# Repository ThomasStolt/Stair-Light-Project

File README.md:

# Stair Light Project

Automatic animated stair lighting with **SK6812 RGBW** LEDs. Two PIR sensors (SR-HC501) at the first and last step detect direction and trigger a random animation. Control via a phone-friendly **web UI** (motion automation on/off, playing animations, fixed colour, device status, settings and birthdays) and optional **night mode** (configurable hours: soft red light only).

- **MCU:** ESP8266 (e.g. NodeMCU)
- **LEDs:** SK6812 RGBW (WS2812-compatible), 27 LEDs per step, 16 steps (configurable)
- **Sensors:** PIR1 = “up”, PIR2 = “down”
- **Boot:** Three soft green-white pulses (2 s) signal “ready”. Motion automation comes back as it was last set (on for a new device).

<div align="center">
  
</div>

---

## Requirements

- **Arduino CLI** (e.g. `brew install arduino-cli`)
- **ESP8266 core:**  
  `arduino-cli core update-index && arduino-cli core install esp8266:esp8266`
- **Libraries:**  
  `arduino-cli lib install "Adafruit NeoPixel"`  
  `arduino-cli lib install "EasyNTPClient"`

---

## Project structure

| Folder/File | Description |
|-------------|-------------|
| `rgbw_stair_light/` | Main sketch (stair light + OTA) |
| `rgbw_stair_light/parking.h` | Animations and helpers |
| `rgbw_stair_light/web_ui.h` | Web UI page (HTML/CSS/JS, served from flash) |
| `rgbw_stair_light/birthdays.h.example` | Template for birthdays (copy to `birthdays.h`) |
| `schematics/` | KiCad schematic, PCB |
| `images/` | Photos (incl. test bed) |

**Scripts (project root):**

| Script | Purpose |
|--------|---------|
| `upload-to-esp8266.sh` | Compile + upload **via USB** |
| `upload-to-esp8266-ota.sh` | Upload **via OTA** (WiFi) to one or more devices; compiles only when the sketch changed |
| `upload-ota-firewall-ok.sh` | OTA with **firewall temporarily disabled** (macOS) |
| `setup-firewall-ota.sh` | Add firewall rule for OTA (macOS, sudo) |

---

## Setup

### 1. WiFi and hostname

Credentials go in **`rgbw_stair_light/credentials.h`** (gitignored).

- Copy `credentials.h.example` to `credentials.h` and set:
  - `WIFI_SSID` – your Wi‑Fi name  
  - `WIFI_PASS` – Wi‑Fi password  
  - `OTA_HOSTNAME` – e.g. `stairlight-testbed` or `stairlight`

Without `credentials.h` the build fails.

> The hostname can also be changed at runtime in the web UI (**Settings** section); it is stored in flash and applied on the next reboot. `OTA_HOSTNAME` in `credentials.h` is only the default used on first boot.

### 2. Birthdays (optional)

On dates listed in **`rgbw_stair_light/birthdays.h`**, only the birthday animation runs.

- **`birthdays.h`** is in `.gitignore` and is not committed.
- Copy `birthdays.h.example` to `birthdays.h`, set `BIRTHDAY_COUNT` and the `BIRTHDAY(month, day)` list (e.g. `BIRTHDAY(3, 15)` = 15 March).
- Without `birthdays.h` the build fails – after cloning, copy the example (use 0 entries if you don’t need birthdays).

### 3. Firewall (macOS, only if OTA fails)

If OTA fails with the firewall on:

- **Option A – rule via CLI:**  
  `sudo ./setup-firewall-ota.sh`  
  (allows Arduino Python and Terminal/Cursor to accept incoming connections)

- **Option B – OTA with firewall briefly off:**  
  `./upload-ota-firewall-ok.sh stairlight-testbed.local`  
  (firewall is disabled only during the upload, then re-enabled)

---

## First upload: via USB

1. Connect the ESP8266 via USB.
2. Check port (optional):  
   `arduino-cli board list`
3. From the project folder run:

   ```bash
   ./upload-to-esp8266.sh
   ```

   Default port is `/dev/cu.usbserial-0001`. To use another port:

   ```bash
   ./upload-to-esp8266.sh /dev/cu.wchusbserial-12345
   ```

4. After a successful upload the ESP connects to Wi‑Fi and is ready for OTA.

---

## Upload via OTA (WiFi)

Prerequisite: the ESP is already running firmware with **ArduinoOTA** (e.g. after the first USB upload) and is on the same Wi‑Fi network. The OTA script uses **espota.py** (no board discovery required); pass the ESP’s IP or mDNS hostname.

- **By hostname (mDNS):**  
  ```bash
  ./upload-to-esp8266-ota.sh stairlight-testbed.local
  ```

- **By IP:**  
  ```bash
  ./upload-to-esp8266-ota.sh 192.168.2.185
  ```

- **Several devices in one go** (same build for all, password asked once):  
  ```bash
  ./upload-ota-firewall-ok.sh 192.168.1.50 192.168.1.51
  ```

The IP is shown in the serial monitor after “Connected, IP address:” or “Web server: http://…”.

**Web UI:** Open `http://<IP>` or `http://<hostname>.local` in a browser. The page is made for phones. Its fonts load from Google Fonts when the phone has internet; without internet it uses the system font.

- **Header** – Device name, WiFi network and the device's local time (NTP).
- **Notices** – Night mode with its hours (“Night mode active” during night hours), and “Not connected, retrying” when the device can't be reached.
- **Motion automation** – On/off switch. The setting is saved on the device and survives restarts and power cuts.
- **Play an animation** – Tiles with live previews: Rainbow, Star sparkle, Birthday, Night red, White ramp and Matrix. A tap plays the animation for 10 s (Matrix: 60 s, `MATRIX_WEB_MS`). The tile of the animation that is running, whether started from the page or by motion, shows a progress ring.
- **Fixed colour** – Sliders for the red, green, blue and white LEDs (0–100 %) with a colour preview, and **All** presets (Off, 25 %, 50 %, 75 %, 100 %). Shown on the stairs while motion automation is off.
- **Recent motion** – The last 5 motion triggers with direction, animation and time.
- **Device** – Memory, flash and WiFi signal at a glance (percent and absolute values), last restart and uptime, plus a table with IP, gateway, DNS, network and channel, access point, reconnects, CPU, restart reason, free memory, largest free block, fragmentation and space left for updates.
- **Settings** – Device name (applied after a restart), night mode on/off and its hours.
- **Birthdays** – Add, edit and remove up to 20 birthdays.
- **Restart device** – With a confirmation on the page.
- **Firmware version** – At the bottom of the page.

The browser caches the page for an hour, so reload it after a firmware update. The page talks to the device through a small JSON API: `GET /api/state` (automation, colour, night mode, running animation), `/api/time`, `/api/log`, `/api/memory`, `/api/sysinfo`, `/api/settings`, `/api/birthdays`, and `POST /api/auto`, `/api/color`, `/api/play` (`anim=2..7`), `/api/settings`, `/api/birthdays`, `/api/reboot`. The web server keeps answering while an animation runs; OTA uploads only work between animations.

**If the firewall (macOS) blocks OTA:**  
Use the wrapper script instead of `upload-to-esp8266-ota.sh`:

```bash
./upload-ota-firewall-ok.sh stairlight-testbed.local
```

The firewall is then disabled only during the upload and re-enabled afterwards.

**espota debug output:**  
```bash
./upload-to-esp8266-ota.sh stairlight-testbed.local --debug
```

---

## Serial monitor

Baud rate: **115200**.

- **Via task (Cursor/VS Code):**  
  `Cmd+Shift+P` → “Tasks: Run Task” → “Serial Monitor (115200 Baud)” → enter port.

- **Via terminal:**  
  ```bash
  arduino-cli monitor -p /dev/cu.usbserial-0001 -c baudrate=115200
  ```

Adjust the port if needed (`arduino-cli board list`). Exit with `Ctrl+C`. While the monitor is running the USB port is in use (no upload).

**Note:** With `USE_SERIAL.setDebugOutput(true)` in the sketch, the ESP8266 WiFi library also prints connection messages (`state:`, `reconnect`, `scandone`, etc.). For a quieter monitor you can set `setDebugOutput(false)` to see only PIR/NTP and your own messages.

---

## Night mode (1–6 h)

Between **1:00 and 6:00 local time** (NTP + auto CET/CEST):

- Only the **night animation** runs: soft breathing red, max 20% brightness, **never fully off** (minimum brightness is configurable).
- PIR triggers the night animation; manual web colours have no effect.
- After 6:00 the strip turns off and normal behaviour (automation/manual) applies again.
- The web UI shows a **“Night mode active”** notice during night hours.

The night animation can be tested anytime in the web UI: tap **Night red** under **Play an animation** (10 s).

---

## Birthdays

Birthdays (month, day, and an optional name) trigger the birthday animation on the day.
They are editable in the web UI under **Birthdays** — add or remove rows and click Save —
and are stored in flash (up to 20 entries), surviving reboots. `birthdays.h` is only the
first-boot default; after that the saved list is authoritative.

API:

```bash
curl http://<host>/api/birthdays
# [{"m":11,"d":19,"name":"Anna"}, ...]
```

`POST /api/birthdays` replaces the whole list (form-encoded: `count=N` then `m<i>`,
`d<i>`, `n<i>` for each entry). Months 1–12, days 1–31, names up to 19 characters
(letters, digits, space, `-` `_` `.`).

## External control API

Another process on the same network can drive the strip directly, bypassing motion
detection — e.g. a parking/garage helper signalling stop/go.

`POST /api/ext` with form field `state`:

| `state`      | Effect                                                        |
|--------------|---------------------------------------------------------------|
| `red`        | Solid red, held until the next command                        |
| `red_blink`    | Red blinking every 500 ms                                   |
| `green_fade`   | Green dimming from full to off over ~30 s, then auto-clears |
| `yellow_blink` | Yellow (red + green) blinking every 500 ms                  |
| `clean`        | All LEDs fade up to near-max (R+G+B+W = 250) for cleaning; fades out on stop; auto-off after 10 min |
| `clear`        | LEDs off immediately, override released                     |

While a command is active, motion detection is suppressed. After `green_fade` finishes
(or `clear`), normal behaviour resumes — daytime automation, or night mode if within
the configured night hours. No authentication (trusted LAN only). An `/api/ext` command
also **interrupts a running motion animation** (it aborts within ~1–2 s rather than
waiting for the animation and its post-delay to finish).

The held states (`red`, `red_blink`, `yellow_blink`) stay active until the next command,
but have a **5-minute safety timeout**: if no new `/api/ext` command arrives within 5
minutes, the override releases automatically and normal operation resumes (so the stairs
can't get stuck if the controller crashes or loses WiFi). Each command resets the timer.
`green_fade` self-terminates after ~30 s.

```bash
curl -X POST -d state=red        http://<host>/api/ext
curl -X POST -d state=red_blink    http://<host>/api/ext
curl -X POST -d state=green_fade   http://<host>/api/ext
curl -X POST -d state=yellow_blink http://<host>/api/ext
curl -X POST -d state=clean        http://<host>/api/ext
curl -X POST -d state=clear        http://<host>/api/ext
```

### Siri / Apple Shortcuts ("Staubsaugen")

Siri can't call the ESP directly, but an Apple **Shortcut** can, and Siri runs Shortcuts by
name. Create two shortcuts in the Shortcuts app (iPhone/iPad/Mac):

1. **"Staubsaugen"** (cleaning light on):
   - Add action **Get Contents of URL**
   - URL: `http://stairlight.local/api/ext` (or the device IP, e.g. `http://<device-ip>/api/ext`)
   - Method: **POST**, Request Body: **Form**, add field `state` = `clean`
2. **"Staubsaugen aus"** (off):
   - Same action/URL, field `state` = `clear`

Then say **"Hey Siri, Staubsaugen!"** to turn all LEDs to full brightness (auto-off after
10 minutes) and **"Hey Siri, Staubsaugen aus!"** to turn it off. The device must be reachable
on the same network (mDNS name `stairlight.local`, or use a DHCP-reserved IP).

#### Siri / Kurzbefehle einrichten (Deutsch)

Siri kann den ESP nicht direkt ansprechen, aber Siri führt **Kurzbefehle** (Shortcuts)
per Namen aus. Lege dafür zwei Kurzbefehle in der **Kurzbefehle**-App (iPhone/iPad/Mac) an:

1. **Kurzbefehl „Staubsaugen"** (Licht an):
   - Aktion **„Inhalte von URL abrufen"** hinzufügen
   - URL: `http://stairlight.local/api/ext` (oder die Geräte-IP, z. B. `http://<device-ip>/api/ext`)
   - Auf **▸ Mehr anzeigen** tippen: **Methode** = `POST`, **Anfragetext** = `Formular`,
     Feld **`state`** = `clean`
2. **Kurzbefehl „Staubsaugen aus"** (Licht aus): gleich wie oben, aber Feld **`state`** = `clear`

Dann **„Hey Siri, Staubsaugen!"** schaltet alle LEDs auf volle Helligkeit (sanft hochdimmen,
automatische Abschaltung nach 10 Minuten) und **„Hey Siri, Staubsaugen aus!"** dimmt wieder
herunter. Hinweise: Das iPhone muss im selben WLAN sein; beim ersten Mal fragt iOS nach der
Erlaubnis für das lokale Netzwerk → **Erlauben**. Falls `stairlight.local` nicht auflöst, die
IP verwenden (am besten im Router eine feste IP / DHCP-Reservierung vergeben).

Night mode (enable + start/end hours) and the hostname are configurable in the web UI
**Settings** section and persist across reboots.

---

## Sketch configuration

In **`rgbw_stair_light/rgbw_stair_light.ino`** (and `parking.h`):

| Constant | Meaning | Default |
|----------|---------|---------|
| `STEPS` | Number of steps | 16 |
| `WIDTH` | LEDs per step | 27 |
| `ANIM_DURATION` | Duration of a PIR-triggered animation (ms) | 20000 |
| `POST_ANIM_DELAY_MS` | Delay after animation before next trigger (ms) | 10000 |
| `BRIGHTNESS` | LED brightness 0–255 | 255 |
| `DEBUG` | 1 = PIR/trigger on serial monitor | 1 |
| `TIMEZONE_OFFSET_SEC` | Seconds UTC→local (e.g. 3600 for CET) | 3600 |
| `FW_VERSION` | Firmware version string shown in web UI | "2.1.0" |
| `NIGHT_HOUR_START` / `NIGHT_HOUR_END` | Night mode from hour … to (excl.) | 1, 6 |
| `NIGHT_BRIGHTNESS_MAX` / `NIGHT_BRIGHTNESS_MIN` | Red in night mode max/min (0–255) | 50, 10 |

Pins (see comments in sketch): NeoPixel = GPIO 14 (D5), PIR1 = GPIO 16 (D0), PIR2 = GPIO 4 (D2). Do not use GPIO 15 and 2 (boot behaviour).

---

## Animations

Direction (up/down) is detected via PIR1/PIR2. With stair automation on, a random one of these animations runs (no back-to-back repeat):

- **Rainbow** (`rainbowSteps`) – steps fade in as a wave, colours flow in walking direction  
- **White ramp** (`FadeToFullBrightness`) – all steps to white  
- **Star sparkle** (`starSparkle`) – dark blue backdrop with white stars that light up and fade out  
- **Matrix** (`matrixRain`) – green digital rain falling down the stairs

On **birthdays** (from the web UI / `birthdays.h`) the **birthday animation** runs instead: random colours on about three quarters of the LEDs, each glowing and fading. At night (night mode hours) motion turns on a soft red light (**Night red**, `nightAnimation`).

In the web UI you can play each of these, plus Birthday and Night red, for 10 seconds (Matrix: 60 seconds).

More functions and possible new animations are in **`parking.h`**.

---

## License / contact

Originally from October 2016; sketch and structure have been extended (OTA, credentials, web API, night mode, birthdays, firewall workaround, date/time, reboot, motion log, memory status table, All presets, automation on by default, OTA via espota.py, night mode indicator, firmware version display).

For questions or ideas for new animations, contact the repository owner.

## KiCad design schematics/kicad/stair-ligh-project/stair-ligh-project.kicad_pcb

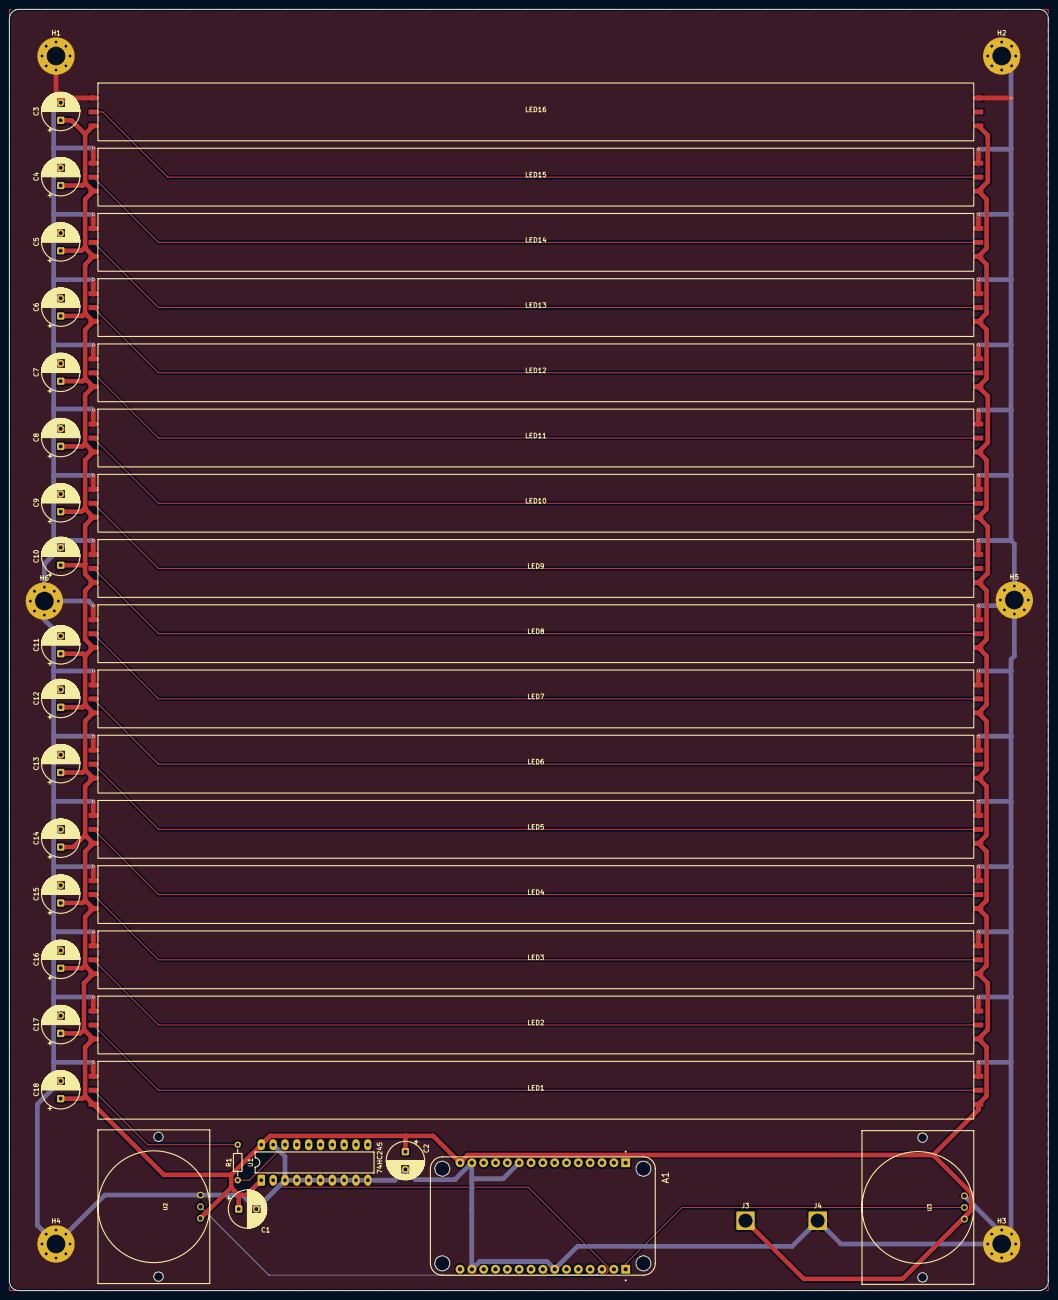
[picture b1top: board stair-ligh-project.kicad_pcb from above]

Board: 2 copper layers, 223.0 x 275.0 mm, 47 parts (0 on the bottom side), 22 nets.

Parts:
A1: 113990105; NodeMCU_v2
C1, C2: 0.1; CP_Radial_D8.0mm_P3.80mm
C3, C4, C5, C6, C7, C8, C9, C10, C11, C12, C13, C14, C15, C16, C17, C18: CP; CP_Radial_D8.0mm_P3.80mm
H1, H2, H3, H4, H5, H6: MountingHole_Pad; MountingHole_4mm_Pad_Via
J3, J4: Conn_01x01; SolderWire-2.5sqmm_1x01_D2.4mm_OD3.6mm
LED1, LED2, LED3, LED4, LED5, LED6, LED7, LED8, LED9, LED10, LED11, LED12, LED13, LED14, LED15, LED16: LED_Row
R1: 470; R_Axial_DIN0204_L3.6mm_D1.6mm_P7.62mm_Horizontal
U1: 74HC245; DIP-20_W7.62mm_LongPads
U2, U3: HC-SR501

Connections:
+5V: A1.J1_15 (VIN), C1.1, C2.1, C3.1, C4.1, C5.1, C6.1, C7.1, C8.1, C9.1, C10.1, C11.1, C12.1, C13.1, C14.1, C15.1, C16.1, C17.1, C18.1, J3.1 (Pin_1_1), LED1.3 (5V), LED1.4 (+5V), LED2.3 (5V), LED2.4 (+5V), LED3.3 (5V), LED3.4 (+5V), LED4.3 (5V), LED4.4 (+5V), LED5.3 (5V), LED5.4 (+5V), LED6.3 (5V), LED6.4 (+5V), LED7.3 (5V), LED7.4 (+5V), LED8.3 (5V), LED8.4 (+5V), LED9.3 (5V), LED9.4 (+5V), LED10.3 (5V), LED10.4 (+5V), LED11.3 (5V), LED11.4 (+5V), LED12.3 (5V), LED12.4 (+5V), LED13.3 (5V), LED13.4 (+5V), LED14.3 (5V), LED14.4 (+5V), LED15.3 (5V), LED15.4 (+5V), LED16.3 (5V), LED16.4 (+5V), U1.1 (A->B), U1.20 (VCC), U2.1 (GND), U3.1 (GND)
GND: A1.J1_10 (GND), A1.J1_14 (GND), A1.J2_7 (GND), A1.J2_14 (GND), C1.2, C2.2, C3.2, C4.2, C5.2, C6.2, C7.2, C8.2, C9.2, C10.2, C11.2, C12.2, C13.2, C14.2, C15.2, C16.2, C17.2, C18.2, H1.1 (1_1), H2.1 (1_1), H3.1 (1_1), H4.1 (1_1), H5.1 (1_1), H6.1 (1_1), J4.1 (Pin_1_1), LED1.1 (GND), LED1.6 (GND), LED2.1 (GND), LED2.6 (GND), LED3.1 (GND), LED3.6 (GND), LED4.1 (GND), LED4.6 (GND), LED5.1 (GND), LED5.6 (GND), LED6.1 (GND), LED6.6 (GND), LED7.1 (GND), LED7.6 (GND), LED8.1 (GND), LED8.6 (GND), LED9.1 (GND), LED9.6 (GND), LED10.1 (GND), LED10.6 (GND), LED11.1 (GND), LED11.6 (GND), LED12.1 (GND), LED12.6 (GND), LED13.1 (GND), LED13.6 (GND), LED14.1 (GND), LED14.6 (GND), LED15.1 (GND), LED15.6 (GND), LED16.1 (GND), LED16.6 (GND), U1.3 (A1), U1.4 (A2), U1.5 (A3), U1.6 (A4), U1.7 (A5), U1.8 (A6), U1.9 (A7), U1.10 (GND), U1.19 (CE), U2.3 (5V), U3.3 (5V)
Level Shifter: A1.J2_8 (D5), U1.2 (A0)
Neopixel: LED1.2 (Din), R1.2
unnamed: LED1.5 (Dout), LED2.2 (Din)
unnamed: LED2.5 (Dout), LED3.2 (Din)
unnamed: LED3.5 (Dout), LED4.2 (Din)
unnamed: LED4.5 (Dout), LED5.2 (Din)
unnamed: LED5.5 (Dout), LED6.2 (Din)
unnamed: LED6.5 (Dout), LED7.2 (Din)
unnamed: LED7.5 (Dout), LED8.2 (Din)
unnamed: LED8.5 (Dout), LED9.2 (Din)
unnamed: LED9.5 (Dout), LED10.2 (Din)
unnamed: LED10.5 (Dout), LED11.2 (Din)
unnamed: LED11.5 (Dout), LED12.2 (Din)
unnamed: LED12.5 (Dout), LED13.2 (Din)
unnamed: LED13.5 (Dout), LED14.2 (Din)
unnamed: LED14.5 (Dout), LED15.2 (Din)
unnamed: LED15.5 (Dout), LED16.2 (Din)
unnamed: R1.1, U1.18 (B0)
PIR1: A1.J2_1 (D0), U3.2 (OUT)
PIR2: A1.J2_3 (D2), U2.2 (OUT)

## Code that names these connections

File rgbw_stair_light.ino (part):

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  #include <avr/power.h>
#endif

#define NEOPIXEL_PIN 14           // which pin are the LEDs connected to?
#define PIR1_PIN 5                // Pin D0 GPIO 5
#define PIR2_PIN 16               // Pin D0 GPIO 16
#define STEPS 5                   // how many steps do the stairs have?
#define WIDTH 27                  // how many LEDs per step do we have?
#define NUM_LEDS  136             // how many LEDs do we have overall?
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
ESP8266WiFiMulti WiFiMulti;

Adafruit_NeoPixel strip = Adafruit_NeoPixel(NUM_LEDS, NEOPIXEL_PIN, NEO_GRBW + NEO_KHZ800);

int gammaw[] = {
    0,  0,  0,  0,  0,  0,  0,  0,  0,  0,  0,  0,  0,  0,  0,  0,
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
  
  strip.setBrightness(BRIGHTNESS);
  strip.begin(); // prepare the data pin for NeoPixel output
  strip.show(); // Initialize all pixels to 'off'
  pinMode(PIR1_PIN, INPUT);
  pinMode(PIR2_PIN, INPUT);
  
}
  
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  uint32 s_timer, c_timer; // start time and current time
  int val1, val2; // Value for PIR Sensor 1 and 2
  while (true) {
    val1 = digitalRead(PIR1_PIN);  // read input value of PIR 1
    val2 = digitalRead(PIR2_PIN);  // read input value of PIR 2
    if (val1 == HIGH) {            // check if the input is HIGH
      Serial.println("UP PIR Sensor 1 Motion detected!");
      s_timer = millis();
      for ( i = 1; i <= STEPS; i++ ) {
        fadeInSingleStep(i, 500, 50, 50, 50, 50);
      }
      val2 = digitalRead(PIR2_PIN);
      c_timer = millis();
      // wait until either time elapsed or second PIR triggered
      while ( ! ( val2 == HIGH || ( c_timer - s_timer > ANIM_DURATION ) ) )   {
        yield();
        delay(100);
        val2 = digitalRead(PIR2_PIN);
        if (val2 == HIGH) {
          Serial.println("UP PIR Sensor 2 Motion detected!");
        }
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      for ( i = STEPS; i >= 1; i-- ) {
        fadeInSingleStep(i, 500, 50, 50, 50, 50);
      }
      val1 = digitalRead(PIR1_PIN);
      c_timer = millis();
      // wait until either time elapsed or second PIR triggered
      while ( ! ( val1 == HIGH || ( c_timer - s_timer > ANIM_DURATION ) ) )   {
        yield();
        delay(100);
        val1 = digitalRead(PIR1_PIN);
        if (val1 == HIGH) {
          Serial.println("UP PIR Sensor 1 Motion detected!");
        }
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
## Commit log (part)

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2018-03-25 first commit on Github
2018-03-25 test
2018-03-29 New changed changes being changed
2018-03-30 first almost working version, it now chooses a random colour, fading out strangely does not work yet
2018-03-30 added some pictures
2018-04-01 cleaning up of code, added starLight function
2018-04-01 code cleaning
2018-04-02 some more code cleaning, the starSparkle function works now
2018-04-02 removed a bug in the stepfade function
2018-09-07 a few changes
2018-11-17 Added schematics
2020-03-16 few changes
2020-11-12 Updated the Parking as well as Stairlight
2020-11-13 never trust ctrl + F
    never only trust ctrl+F to find a certain string, always look throu the
    code manually
2021-11-22 Some Updates to Parking.h and rgbw_stair_light.ion
    This is Currently untested, since I don't have the Test bed with me right now.
    In theory this should Make it so, that between 22:00 and 06:00 the stairs will only be Blue, and If im not Mistaken, it shouldnt even Fade in.
2021-11-23 yehy
2021-11-23 Update RGBWstrandtest.ino
    I finally found the Correct Color, for some nice Blue.
    Now I only need to add the right Time thingy
2026-03-14 Added OTA
2026-03-14 Added WebUI for testing and manual control, added night modus
2026-03-14 English translations
2026-03-14 updated picture
2026-03-14 update picture
2026-03-15 added reboot, status table, movement log and reboot to webUI
2026-06-06 Add EEPROM-backed Settings struct (hostname, night mode)
2026-06-06 Make saveSettings() self-contained with EEPROM.begin() guard
2026-06-06 Drive night mode and hostname from persisted settings
2026-06-06 Add POST /api/ext external control endpoint
2026-06-06 Validate hostname characters (DNS-label) in /api/settings
2026-06-06 Scope color-preset click handler to [data-all] to avoid Save button collision
2026-06-06 Bump to 2.1.0; document external API and configurable settings
2026-06-06 Docs: correct FW_VERSION default and table separator in README
2026-06-06 Use runtime birthday store in isBirthdayToday()
2026-06-06 Add GET/POST /api/birthdays (replace-all, validated, persisted)
2026-06-06 Reject non-numeric count in /api/birthdays (avoid silent list clear)
2026-06-06 Add web UI Birthdays section (list/add/remove/save)
2026-06-06 Bump to 2.2.0; document web-editable birthdays
